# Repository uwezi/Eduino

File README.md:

# Eduino
Another ATmega32U4 breakout board

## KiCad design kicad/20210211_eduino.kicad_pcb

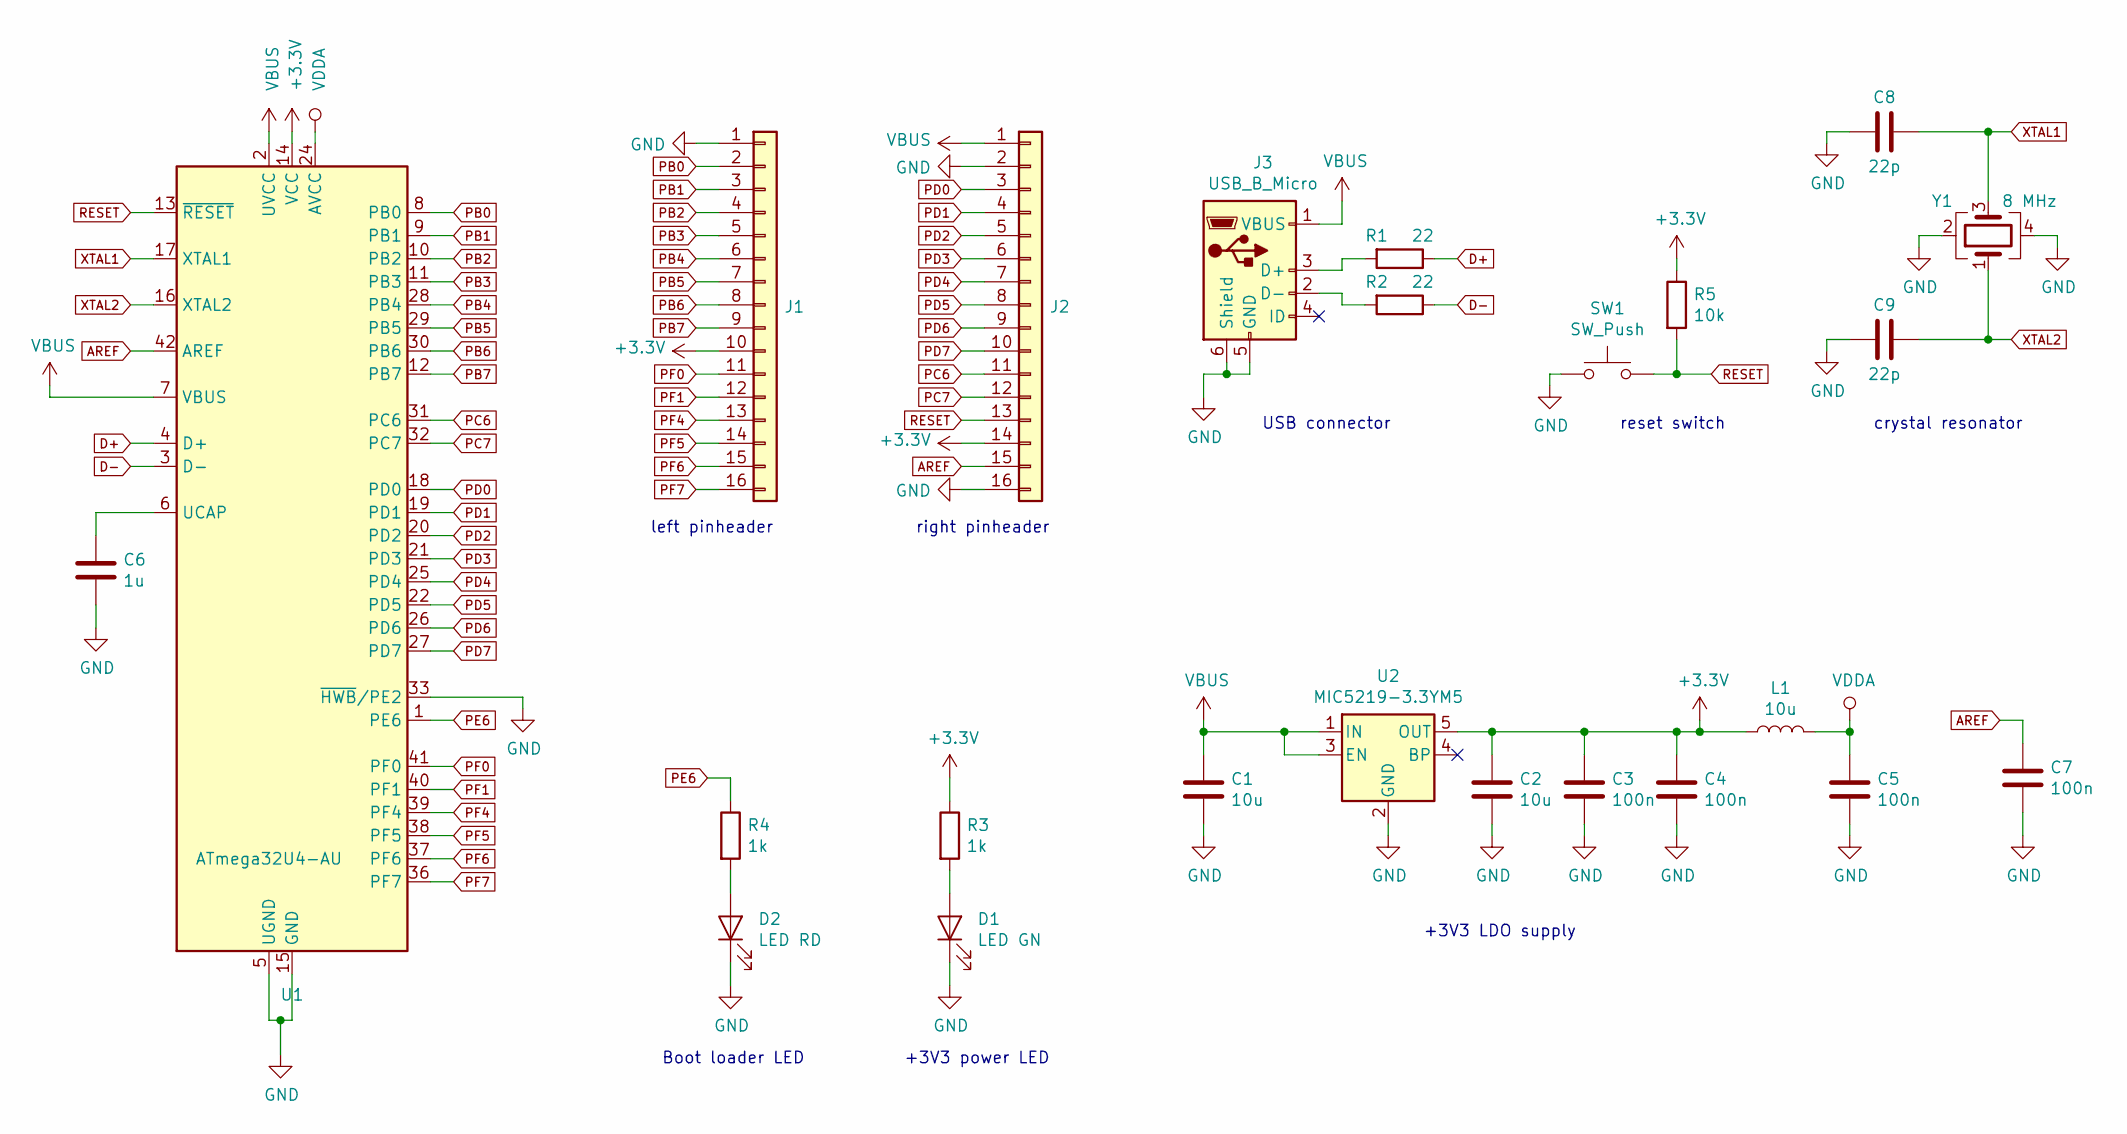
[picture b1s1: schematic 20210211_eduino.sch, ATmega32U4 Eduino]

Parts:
C1, C2: 10u; C_1206_3216Metric
C3, C4, C5, C7: 100n; C_0603_1608Metric
C6: 1u; C_0805_2012Metric
C8, C9: 22p; C_0603_1608Metric
D1: LED GN; LED_0603_1608Metric
D2: LED RD; LED_0603_1608Metric
J1, J2: Conn_01x16; PinHeader_1x16_P2.54mm_Vertical
J3: USB_B_Micro; micro-5P-Flat-welding-High-temperature_C40942
L1: 10u; L_1206_3216Metric
R1, R2: 22; R_0603_1608Metric
R3, R4: 1k; R_0603_1608Metric
R5: 10k; R_0603_1608Metric
SW1: SW_Push; SW_Push_1P1T_NO_6x6mm_H9.5mm
U1: ATmega32U4-AU; TQFP-44_10x10mm_P0.8mm
U2: MIC5219-3.3YM5; SOT-23-5
Y1: 8 MHz; Crystal_SMD_3225-4Pin_3.2x2.5mm

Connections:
+3V3: C2.1, C3.1, C4.1, J1.10, J2.14, L1.1, R3.1, R5.1, U1.14 (VCC), U1.34 (VCC), U2.5 (OUT)
AREF: C7.1, J2.15, U1.42 (AREF)
D+: R1.1, U1.4 (D+)
D-: R2.1, U1.3 (D-)
GND: C1.2, C2.2, C3.2, C4.2, C5.2, C6.2, C7.2, C8.1, C9.1, D1.1 (K), D2.1 (K), J1.1, J2.2, J2.16, J3.5 (GND), J3.6 (Shield), SW1.1, U1.5 (UGND), U1.15 (GND), U1.23 (GND), U1.33 (~HWB~/PE2), U1.35 (GND), U1.43 (GND), U2.2 (GND), Y1.2, Y1.4
unnamed: C6.1, U1.6 (UCAP)
unnamed: C8.2, U1.17 (XTAL1), Y1.3
unnamed: C9.2, U1.16 (XTAL2), Y1.1
unnamed: D1.2 (A), R3.2
unnamed: D2.2 (A), R4.2
unnamed: J3.2 (D-), R2.2
unnamed: J3.3 (D+), R1.2
PB0: J1.2, U1.8 (PB0)
PB1: J1.3, U1.9 (PB1)
PB2: J1.4, U1.10 (PB2)
PB3: J1.5, U1.11 (PB3)
PB4: J1.6, U1.28 (PB4)
PB5: J1.7, U1.29 (PB5)
PB6: J1.8, U1.30 (PB6)
PB7: J1.9, U1.12 (PB7)
PC6: J2.11, U1.31 (PC6)
PC7: J2.12, U1.32 (PC7)
PD0: J2.3, U1.18 (PD0)
PD1: J2.4, U1.19 (PD1)
PD2: J2.5, U1.20 (PD2)
PD3: J2.6, U1.21 (PD3)
PD4: J2.7, U1.25 (PD4)
PD5: J2.8, U1.22 (PD5)
PD6: J2.9, U1.26 (PD6)
PD7: J2.10, U1.27 (PD7)
PE6: R4.1, U1.1 (PE6)
PF0: J1.11, U1.41 (PF0)
PF1: J1.12, U1.40 (PF1)
PF4: J1.13, U1.39 (PF4)
PF5: J1.14, U1.38 (PF5)
PF6: J1.15, U1.37 (PF6)
PF7: J1.16, U1.36 (PF7)
RESET: J2.13, R5.2, SW1.2, U1.13 (~RESET)
VBUS: C1.1, J2.1, J3.1 (VBUS), U1.2 (UVCC), U1.7 (VBUS), U2.1 (IN), U2.3 (EN)
VDDA: C5.1, L1.2, U1.24 (AVCC), U1.44 (AVCC)

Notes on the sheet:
+3V3 power LED
Boot loader LED
left pinheader
right pinheader
+3V3 LDO supply
USB connector
reset switch
crystal resonator

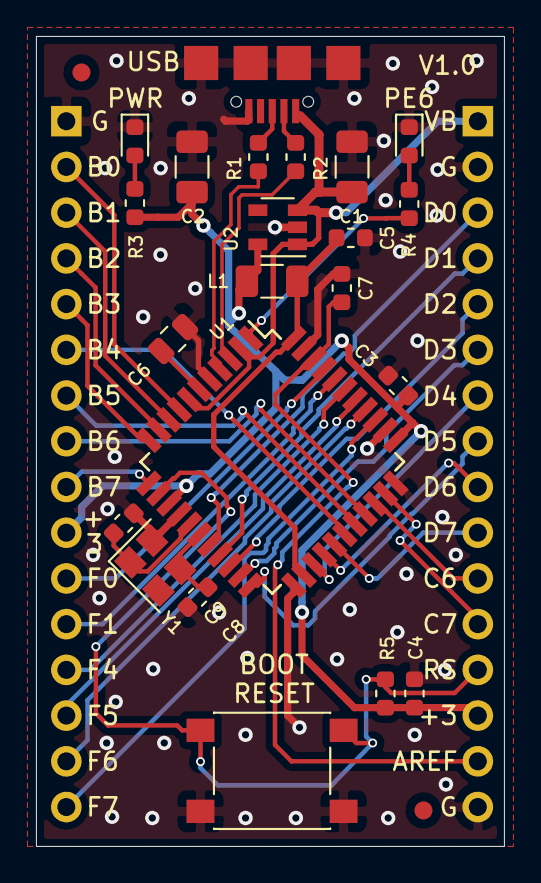
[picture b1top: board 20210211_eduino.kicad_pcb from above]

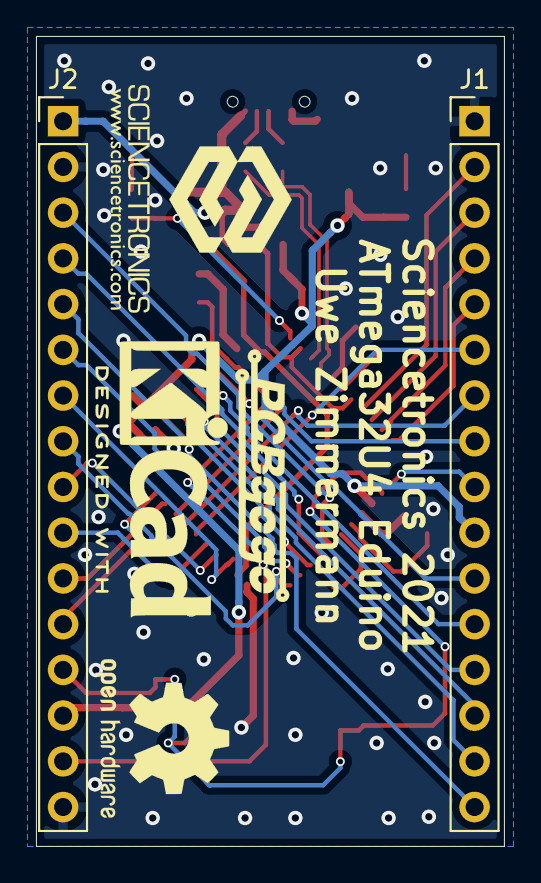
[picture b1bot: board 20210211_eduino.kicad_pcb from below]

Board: 4 copper layers, 26.0 x 45.0 mm, 24 parts (2 on the bottom side), 40 nets.

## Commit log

2021-02-11 Create kicad_files
2021-02-11 Create documentation
2021-09-05 Bootloader
    I added the untidy version of the modified bootloader. There are two .hex files for the ATmega32U4 - one for 8 MHz (recommended at 3.3 V) and one for 16 MHz (on your own risk at 3.3 V).
    Changes made:
    - only one LED in comparison to the original
    - LED is connected to PE6
    Things to do:
    - VID/PID are borrowed from the compatible Sparkfun Pro Micro
2023-02-10 Add files via upload
    added information about PD5 = TLED = Arduino pin #30
